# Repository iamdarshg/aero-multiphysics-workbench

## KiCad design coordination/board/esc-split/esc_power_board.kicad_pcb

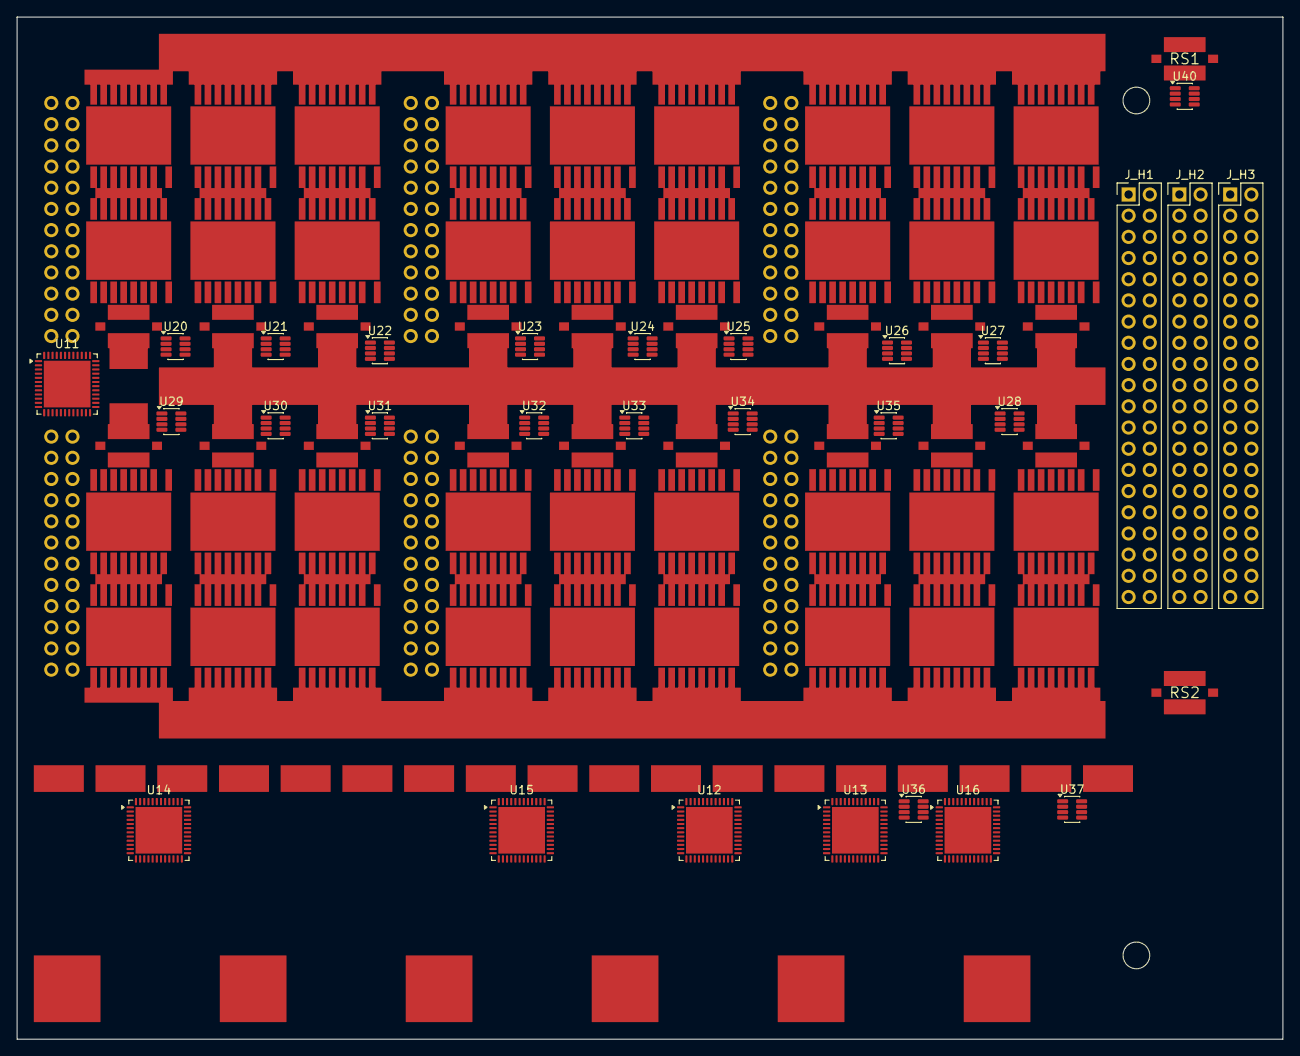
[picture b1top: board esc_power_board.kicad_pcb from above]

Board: 4 copper layers, 151.8 x 122.5 mm, 173 parts (0 on the bottom side), 41 nets, no tracks yet.

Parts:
BAR1, BAR2, BAR3: Busbar_land
C1, C2, C3, C4, C5, C6: 820uF_35V
CB1, CB2, CB3, CB4, CB5, CB6, CB7, CB8, CB9, CB10, CB11, CB12, CB13, CB14, CB15, CB16, CB17, CB18: copper
CN1, CN2, CN3, CN4, CN5, CN6, CN7, CN8, CN9, CN10, CN11, CN12, CN13, CN14, CN15, CN16, CN17, CN18: copper
CP1, CP2, CP3, CP4, CP5, CP6, CP7, CP8, CP9, CP10, CP11, CP12, CP13, CP14, CP15, CP16, CP17, CP18: copper
H4, H5: MountingHole_3.2
J1, J2, J3, J4, J5, J6: Conn_02x12_Pin
J_H1, J_H2, J_H3: TSW-120-15-G-D; PinHeader_2x20_P2.54mm_Vertical
P1, P2, P3, P4, P5, P6, P7, P8, P9, P10, P11, P12, P13, P14, P15, P16, P17, P18: MotorLand_6x4
Q1AH, Q1AL, Q1BH, Q1BL, Q1CH, Q1CL, Q2AH, Q2AL, Q2BH, Q2BL, Q2CH, Q2CL, Q3AH, Q3AL, Q3BH, Q3BL, Q3CH, Q3CL, Q4AH, Q4AL, Q4BH, Q4BL, Q4CH, Q4CL, Q5AH, Q5AL, Q5BH, Q5BL, Q5CH, Q5CL, Q6AH, Q6AL, Q6BH, Q6BL, Q6CH, Q6CL: IPTC014N10NM5
R1A, R1B, R1C, R2A, R2B, R2C, R3A, R3B, R3C, R4A, R4B, R4C, R5A, R5B, R5C, R6A, R6B, R6C: L500x 0.5m 10W
RS1, RS2: L500x 0.5m 10W
U11, U12, U13, U14, U15, U16: DRV8353; QFN-48-1EP_7x7mm_P0.5mm_EP5.6x5.6mm
U20, U21, U22, U23, U24, U25, U26, U27, U28, U29, U30, U31, U32, U33, U34, U35, U36, U37, U40: INA296A2; SOT-23-8

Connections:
AGND: J_H3.2, J_H3.4, J_H3.6, J_H3.8, J_H3.10, J_H3.12, J_H3.14, J_H3.16, J_H3.18, J_H3.20, J_H3.22, J_H3.24, J_H3.26, J_H3.28, J_H3.30, J_H3.32, J_H3.34, J_H3.36, J_H3.38
BATN: BAR2.1, CB1.1, CB2.1, CB3.1, CB4.1, CB5.1, CB6.1, CB7.1, CB8.1, CB9.1, CB10.1, CB11.1, CB12.1, CB13.1, CB14.1, CB15.1, CB16.1, CB17.1, CB18.1, R1A.2, R1B.2, R1C.2, R2A.2, R2B.2, R2C.2, R3A.2, R3B.2, R3C.2, R4A.1, R4B.1, R4C.1, R5A.1, R5B.1, R5C.1, R6A.1, R6B.1, R6C.1
BATN_K: R1A.4, R1B.4, R1C.4, R2A.4, R2B.4, R2C.4, R3A.4, R3B.4, R3C.4, R4A.3, R4B.3, R4C.3, R5A.3, R5B.3, R5C.3, R6A.3, R6B.3, R6C.3
BATP: BAR1.1, BAR3.1, CP1.1, CP2.1, CP3.1, CP4.1, CP5.1, CP6.1, CP7.1, CP8.1, CP9.1, CP10.1, CP11.1, CP12.1, CP13.1, CP14.1, CP15.1, CP16.1, CP17.1, CP18.1, Q1AH.9, Q1BH.9, Q1CH.9, Q2AH.9, Q2BH.9, Q2CH.9, Q3AH.9, Q3BH.9, Q3CH.9, Q4AH.9, Q4BH.9, Q4CH.9, Q5AH.9, Q5BH.9, Q5CH.9, Q6AH.9, Q6BH.9, Q6CH.9
DGND: J_H1.5, J_H1.6, J_H1.7, J_H1.8, J_H1.10, J_H1.12, J_H1.15, J_H1.16, J_H1.20, J_H1.23, J_H1.24, J_H1.27, J_H1.28, J_H1.32, J_H1.40, J_H2.4, J_H2.8, J_H2.12, J_H2.16, J_H2.20, J_H2.24, J_H2.28, J_H2.30, J_H2.34
M1_PHA: CN1.1, Q1AH.1, Q1AL.9
M1_PHB: CN2.1, Q1BH.1, Q1BL.9
M1_PHC: CN3.1, Q1CH.1, Q1CL.9
M1_SNA: Q1AL.1, R1A.1
M1_SNB: Q1BL.1, R1B.1
M1_SNC: Q1CL.1, R1C.1
M2_PHA: CN4.1, Q2AH.1, Q2AL.9
M2_PHB: CN5.1, Q2BH.1, Q2BL.9
M2_PHC: CN6.1, Q2CH.1, Q2CL.9
M2_SNA: Q2AL.1, R2A.1
M2_SNB: Q2BL.1, R2B.1
M2_SNC: Q2CL.1, R2C.1
M3_PHA: CN7.1, Q3AH.1, Q3AL.9
M3_PHB: CN8.1, Q3BH.1, Q3BL.9
M3_PHC: CN9.1, Q3CH.1, Q3CL.9
M3_SNA: Q3AL.1, R3A.1
M3_SNB: Q3BL.1, R3B.1
M3_SNC: Q3CL.1, R3C.1
M4_PHA: CN10.1, Q4AH.1, Q4AL.9
M4_PHB: CN11.1, Q4BH.1, Q4BL.9
M4_PHC: CN12.1, Q4CH.1, Q4CL.9
M4_SNA: Q4AL.1, R4A.2
M4_SNB: Q4BL.1, R4B.2
M4_SNC: Q4CL.1, R4C.2
M5_PHA: CN13.1, Q5AH.1, Q5AL.9
M5_PHB: CN14.1, Q5BH.1, Q5BL.9
M5_PHC: CN15.1, Q5CH.1, Q5CL.9
M5_SNA: Q5AL.1, R5A.2
M5_SNB: Q5BL.1, R5B.2
M5_SNC: Q5CL.1, R5C.2
M6_PHA: CN16.1, Q6AH.1, Q6AL.9
M6_PHB: CN17.1, Q6BH.1, Q6BL.9
M6_PHC: CN18.1, Q6CH.1, Q6CL.9
M6_SNA: Q6AL.1, R6A.2
M6_SNB: Q6BL.1, R6B.2
M6_SNC: Q6CL.1, R6C.2

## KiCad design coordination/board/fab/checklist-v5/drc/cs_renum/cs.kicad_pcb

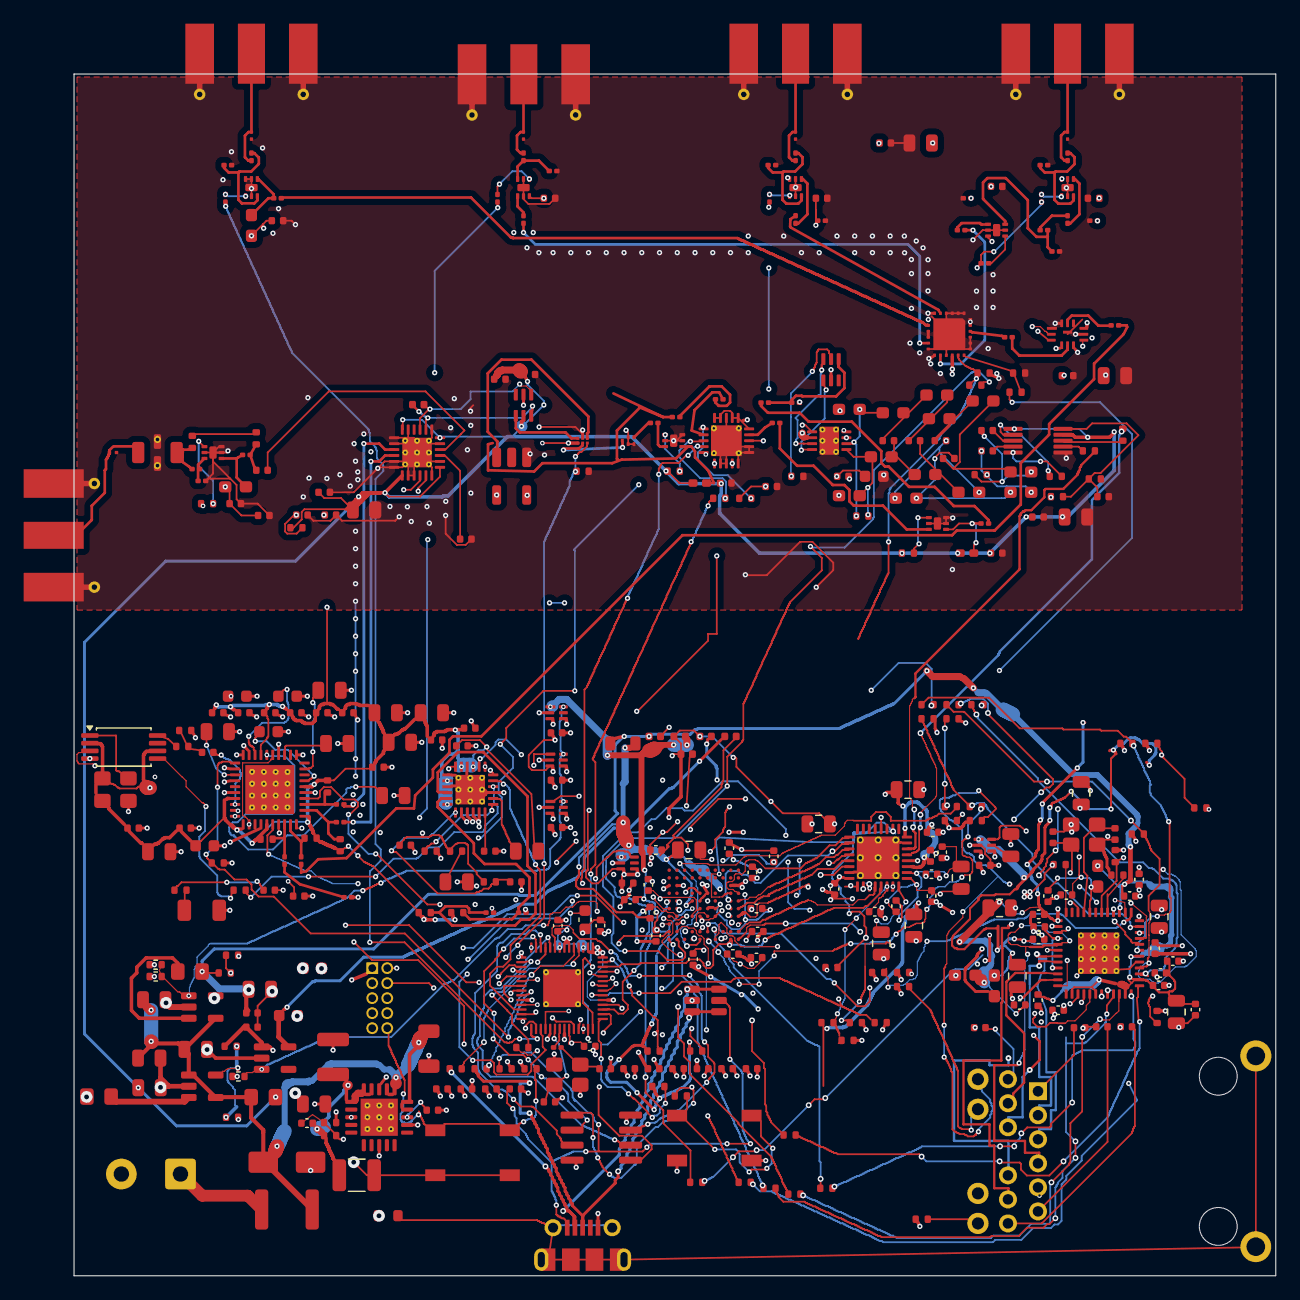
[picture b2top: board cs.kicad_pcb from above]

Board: 4 copper layers, 101.6 x 101.6 mm, 373 parts (0 on the bottom side), 260 nets.

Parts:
C1, C2, C4, C7: 22uF; C_0805_2012Metric
C3, C6, C41, C43, C45, C56, C57, C58, C61, C62, C65, C66, C67, C73, C83, C94, C106, C154, C159, C261, C279, C280, C281, C297, C300, C310: 10uF; C_0805_2012Metric
C5, C8, C23, C24, C25, C26, C27, C28, C40, C42, C44, C46, C47, C48, C50, C51, C52, C53, C54, C55, C60, C69, C76, C77, C78, C81, C82, C93, C100, C101, C105, C150, C151, C152, C153, C155, C174, C200, C214, C224, C225, C226, C227, C254, C255, C256, C260, C270, C272, C273, C274, C275, C276, C277, C278, C283, C284, C293, C295, C296, C298, C299, C302, C303, C304, C305, C307, C308, C309, C311, C312, C314, C316, C318, C319, C321, C322, C330, C331, C340, C341, C342, C343, C344, C347: 100nF; C_0402_1005Metric
C9, C22, C63, C64, C68, C247, C271: 1uF; C_0603_1608Metric
C10: 2.2uF; C_0603_1608Metric
C11: 22uF_10V_X7R; C_1206_3216Metric
C12, C346: 47uF_10V_X7R; C_1210_3225Metric
C20, C21: 15pF_C0G; C_0402_1005Metric
C70: 4.7nF_C0G; C_0402_1005Metric
C71: 100nF_C0G; C_1206_3216Metric
C72, C156, C301, C348: 10nF; C_0402_1005Metric
C74, C205: 470pF_C0G; C_0402_1005Metric
C75: 22nF_C0G; C_0805_2012Metric
C80, C213, C282: 100pF_C0G; C_0402_1005Metric
C102, C211, C212: 1nF_C0G; C_0402_1005Metric
C157, C158: 33pF_C0G; C_0402_1005Metric
C201, C202, C203, C204, C206, C207, C208, C210, C215, C223, C232, C233, C234, C235, C236, C237, C238, C245: 100pF_C0G; C_0201_0603Metric
C209, C219, C292, C2112: 0.2pF_C0G; C_0201_0603Metric
C216: 0.6pF_C0G; C_0201_0603Metric
C217: 0.8pF_C0G; C_0201_0603Metric
C218, C291: 0.5pF_C0G; C_0201_0603Metric
C246, C294, C2211: 1.0pF_C0G; C_0201_0603Metric
C262, C268: 51pF_C0G; C_0402_1005Metric
C264, C266: 56pF_C0G; C_0402_1005Metric
C306, C313, C323: 1uF; C_0402_1005Metric
C315, C317, C320: 2.2uF; C_0402_1005Metric
C345: 20nF_C0G_5%; C_0805_2012Metric
C2110: 22pF_C0G; C_0201_0603Metric
C2111: 0.3pF_C0G; C_0201_0603Metric
C2210: 2.2pF_C0G; C_0201_0603Metric
D1: SMAJ5.0A; D_SMA
D50, D60, D61, D62, D63: PESD1V0R1BCSF; SOD962-2_DSN0603
F1: 2.5A_PTC; Fuse_1812_4532Metric
FB1: 600R@100MHz_2A; Inductor_0805_HandSolder
FB30: 600R@100MHz; L_0603_1608Metric_Pad1.05x0.95mm_HandSolder
FB31, FB32: 120R@100MHz; L_0603_1608Metric_Pad1.05x0.95mm_HandSolder
FB33: BLM21SN300SN1D; L_0805_2012Metric
FB34: 220R@100MHz; L_0402_1005Metric
FB35, FB36, FB37, FB38: 120R@100MHz; L_0402_1005Metric
FL50: LFCN-2500+; MiniCircuits_FV1206
FL70: QPQ1909TR13; QPQ1909_1.4x1.2mm
J1: 5V_INPUT_ONLY; TerminalBlock_Phoenix_MKDS-1,5-2_1x02_P5.00mm_Horizontal
J10: USB_B_Micro; USB_Micro-B_Molex-105017-0001
J11: Cortex_SWD_10pin; PinHeader_2x05_P1.27mm_Vertical
J30: JK0654219NL; RJ45_Pulse_JK0654219NL_Horizontal
J50: RF_LOW_0.01_2.5GHz_OPTION; SMA_Molex_73251-1153_EdgeMount_Horizontal
J60: RF_HIGH_2.3_4.2GHz; SMA_Molex_73251-1153_EdgeMount_Horizontal
J61: RF_HIGH_4.2_6.8GHz; SMA_Molex_73251-1153_EdgeMount_Horizontal
J62: RF_HIGH_6.8_9.2GHz; SMA_Molex_73251-1153_EdgeMount_Horizontal
J63: RF_HIGH_8.0_10GHz; SMA_Molex_73251-1153_EdgeMount_Horizontal
L1, L2: 2.2uH_2.5A; Inductor_0805_HandSolder
L80, L83: 220nH; L_0603_1608Metric_Pad1.05x0.95mm_HandSolder
L84, L97: 33nH; L_0402_1005Metric_Pad0.77x0.64mm_HandSolder
L85, L86: 2.2uH; L_0603_1608Metric_Pad1.05x0.95mm_HandSolder
L87, L88, L95, L96: 200nH; L_0603_1608Metric_Pad1.05x0.95mm_HandSolder
L89, L90, L93, L94: 360nH; L_0603_1608Metric_Pad1.05x0.95mm_HandSolder
L91, L92: 390nH; L_0603_1608Metric_Pad1.05x0.95mm_HandSolder
L98: 2.7nH; L_0402_1005Metric
R1: 453k_0.1%; R_0402_1005Metric
R2, R4: 100k_0.1%; R_0402_1005Metric
R3: 101k_0.1%; R_0402_1005Metric
R5: 0; R_0603_1608Metric
R20, R21: 27R; R_0402_1005Metric
R22, R23, R146: 100k; R_0402_1005Metric
R30, R33, R134, R135, R136, R137, R138, R139, R140, R148: 4.7k; R_0402_1005Metric
R31, R51, R120, R121, R122, R123, R124, R125, R126, R127, R128, R129, R130, R131, R149: 33R; R_0402_1005Metric
R32, R60, R153, R156: 0R; R_0402_1005Metric
R40: 12.1k_1%; R_0402_1005Metric
R41, R141, R142, R143, R147: 10k; R_0402_1005Metric
R42, R43: 330R; R_0402_1005Metric
R50, R152: 150R_1%; R_0402_1005Metric
R52, R53, R54, R55: 50R; R_0402_1005Metric
R56, R93: 220R_1%; R_0402_1005Metric
R58: 4.7k_1%; R_0402_1005Metric
R59, R160, R161: 1k_1%; R_0402_1005Metric
R61: 1.5k_1%; R_0402_1005Metric
R70, R81: 499R_1%; R_0402_1005Metric
R71: 3.0R_1%; R_0402_1005Metric
R72: 33R_1%; R_0402_1005Metric
R73, R74: 25R_1%; R_0402_1005Metric
R75, R76, R77, R78, R144, R145: 10k_1%; R_0402_1005Metric
R79, R80: 100R_1%; R_0402_1005Metric
R90: 2.00k_1%; R_0402_1005Metric
R91: 1.00k_1%; R_0402_1005Metric
R92: 50R; R_0201_0603Metric
R94, R95: 51R; R_0402_1005Metric
R100, R105, R106, R107, R111: 0R; R_0201_0603Metric
R101: 1.5k; R_0201_0603Metric
R102: 200R; R_0201_0603Metric
R103, R112: 2.9k; R_0201_0603Metric
R132, R133: 2.2k; R_0402_1005Metric
R150: 1k; R_0201_0603Metric
R151: 1k; R_0402_1005Metric
R154: 30.3k_0.1%; R_0402_1005Metric
R155: 10k_0.1%; R_0402_1005Metric
R157, R159: 120k_1%; R_0402_1005Metric
R158: 100k_1%; R_0402_1005Metric
SW1: BOOTSEL; SW_SPST_TL3342
SW2: RESET; SW_SPST_TL3342
T50: 2450BL15B0200001E; Johanson_0805_6P_Balun
T60: TC1-1-13M+; Transformer_MiniCircuits_AT224-1A
T70: 2450BL15B0100001E; Johanson_0805_6P_Balun
U1, U2: TLV62569DBVR; SOT-23-5
U3: TLV75525PDBVR; SOT-23-5
U4: TPS7A8300ARGWT; Texas_RGW0020A_VQFN-20-1EP_5x5mm_P0.65mm_EP3.15x3.15mm_Ther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
U5, U6, U7: TPS389033DSER; WSON-6_1.5x1.5mm_P0.5mm
U8, U9: TPS389012DSER; WSON-6_1.5x1.5mm_P0.5mm
U10: RP2040; QFN-56-1EP_7x7mm_P0.4mm_EP3.2x3.2mm_ThermalVias
U11: W25Q16JVSNIQ; SOIC-8_3.9x4.9mm_P1.27mm
U12: USBLC6-2SC6; SOT-23-6
U20: LIF-MD6000-6JMG80I
U21: AD9215BCPZ-105; LFCSP-32-1EP_5x5mm_P0.5mm_EP3.6x3.6mm_ThermalVias
U30: KSZ9031RNXCA; QFN-48-1EP_7x7mm_P0.5mm_EP3.5x3.5mm_ThermalVias
U40: LMX2592RHAT; Texas_RHA0040B_VQFN-40-1EP_6x6mm_P0.5mm_EP4.15x4.15mm_Therm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
U41: ADF4360-1BCPZ; LFCSP-24-1EP_4x4mm_P0.5mm_EP2.5x2.5mm_ThermalVias
U42: CDCLVC1104PWR; TSSOP-8_4.4x3mm_P0.65mm
U50, U60: GRF4001; GRF_DFN6_1.5x1.5mm
U51: ADL5801ACPZ-R7; LFCSP-24-1EP_4x4mm_P0.5mm_EP2.5x2.5mm_ThermalVias
U61, U62, U66, U67: GRF2101; GRF_DFN6_1.5x1.5mm
U63: LTC5548IUDB; DFN-12-1EP_3x2mm_P0.5mm
U64: QPC6144TR13; QPC6144_LGA24_4x4mm
U70: BGS12WN6E6327; Infineon_TSNP6_1.1x0.7mm
U71, U75: GRF2013; GRF_DFN6_1.5x1.5mm
U72: PE4312C-Z; QFN-20-1EP_4x4mm_P0.5mm_EP2.6x2.6mm_ThermalVias
U73: LT5560EDD; DFN-8-1EP_3x3mm_P0.5mm_EP1.65x2.38mm_ThermalVias
U74: AD8351ARMZ; MSOP-10_3x3mm_P0.5mm
Y10: ABM8-272-T3_12MHz; Crystal_SMD_3225-4Pin_3.2x2.5mm
Y30: ECS-250-20-33-TR_25MHz; Crystal_SMD_3225-4Pin_3.2x2.5mm
Y40: SiT8209AC-23-33E-100.000000X; Oscillator_SMD_SiT_PQFN-4Pin_3.2x2.5mm

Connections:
+1V2_CORE: C7.1, C8.1, C52.1, C53.1, C54.1, C57.1, C303.1, C304.1, C305.1, FB30.1, FB32.1, FB33.1, FB34.1, L2.2, R3.1, U30.14, U30.18, U30.23, U30.26, U30.30, U30.39
+2V5_AUX: C10.1, FB38.1, U3.5
+3V3_ANA: C12.1, C40.1, C41.1, C44.1, C45.1, C60.1, C61.1, C69.1, C73.2, C76.1, C77.1, C78.1, C80.1, C81.1, C93.1, C94.1, C102.1, C224.1, C225.1, C226.1, C227.1, C247.1, C260.1, C261.1, C270.1, C271.1, C273.1, C274.1, C275.1, C276.1, C277.1, C278.1, C279.1, C280.1, C281.1, C293.1, C294.1, C346.1, C348.1, C2210.1, C2211.1, L80.1, L83.1, L85.1, L86.1, R52.1, R53.1, R54.1, R55.1, R75.1, R90.1, R94.1, R95.1, R154.1, U4.1, U4.19, U4.20, U21.27, U21.32, U40.7, U40.11, U40.15, U40.21, U40.26, U40.37, U41.2, U41.6, U41.21, U41.23, U42.2, U42.6, U61.6, U62.6, U63.9, U64.16, U66.6, U67.6, U73.2, U73.7, Y40.1, Y40.4
+3V3_DIG: C4.1, C5.1, C9.1, C23.1, C24.1, C25.1, C26.1, C27.1, C28.1, C42.1, C43.1, C50.1, C51.1, C56.1, C101.1, C302.1, C306.1, C307.1, C308.1, C309.1, C340.1, C341.1, C342.1, C343.1, C344.1, FB31.1, FB35.1, FB36.1, FB37.1, J11.1, L1.2, R1.1, R23.1, R41.1, R42.1, R43.1, R78.1, R132.1, R133.1, R134.1, R135.1, R136.1, R137.1, R141.1, R142.1, R157.1, R159.1, U3.1, U5.3, U5.4, U6.3, U6.4, U7.3, U7.4, U8.3, U8.4, U9.3, U9.4, U10.1, U10.10, U10.22, U10.33, U10.42, U10.43, U10.44, U10.48, U10.49, U11.8, U21.16, U30.16, U30.34, U30.40, U70.4, U72.6, U72.9, U72.13, U72.15, U72.16, U72.17, U72.19, U72.20
+5V_RF: C2.1, C82.1, C83.1, C100.1, C105.1, C106.1, C282.1, C283.1, C284.1, FB1.2, L84.1, L97.1, R61.1, R70.1, R81.1, T50.2, U51.7, U51.13, U51.18, U51.24, U74.1, U74.9
AD8351_IN_N: C255.2, U74.4
AD8351_IN_P: C254.2, U74.3
AD8351_OUT_N: R74.1, U74.7
AD8351_OUT_P: R73.1, U74.8
AD8351_RGP1: R72.1, U74.2
AD8351_RGP2: R72.2, U74.5
ADC_CLK: R31.2, U20.D9, U21.2
ADC_D0: U20.D10, U21.9
ADC_D1: U20.E9, U21.10
ADC_D2: U20.E10, U21.11
ADC_D3: U20.F9, U21.12
ADC_D4: U20.F10, U21.13
ADC_D5: U20.G9, U21.14
ADC_D6: U20.G10, U21.17
ADC_D7: U20.H9, U21.18
ADC_D8: U20.H10, U21.19
ADC_D9: U20.J10, U21.20
ADC_MODE: C156.1, R90.2, R91.1, U21.22
ADC_OR: U10.40, U20.K9, U21.21
ADC_PDWN: R147.1, U10.34, U21.4
ADC_REFB: C47.1, C154.2, C155.2, U21.25
ADC_REFT: C48.1, C154.1, C155.1, U21.26
ADC_SENSE: R32.1, U21.23
ADC_VCM: C256.1, R75.2, R76.1, U74.10
ADC_VIN_N: R74.2, U21.30
ADC_VIN_P: R73.2, U21.29
ADC_VREF: C46.1, C159.1, U21.24
ADF_CC: C72.1, U41.12
ADF_CLK: U10.12, U41.17
ADF_CN: C73.1, U41.14
ADF_CPOUT: C74.1, R59.1, R93.1, U41.24
ADF_DATA: U10.13, U41.18
ADF_LE: U10.11, U41.19
ADF_LF1: C75.1, R59.2
ADF_LO2_N_RAW: C207.1, R95.2, U41.5
ADF_LO2_P_RAW: C206.1, R94.2, U41.4
ADF_LOCK: U10.39, U41.20
ADF_REF: R51.2, U41.16
ADF_RSET: R58.1, U41.13
ADF_VTUNE: C205.1, R93.2, U41.7
ADL_DETO: C214.1, U51.11
ADL_RF_DRIVE: C211.2, U51.16
ADL_RF_UNUSED: C212.1, U51.15
ADL_VSET: C213.1, R61.2, U51.10
ANA_NR_SS: C347.1, U4.13
AUX_EN: R159.2, U3.3, U8.6
BOOTSEL_SWITCH: R151.2, SW1.D36_0, SW1.D36_1
CHASSIS_GND: J10.D55_5, J10.D55_6, J10.D55_7, J10.D55_8, J10.D55_9, J10.D55_10, J10.D55_11, J10.D55_12, J30.D14_18, J30.D14_19, R5.2
CORE_EN: R157.2, R158.1, U2.1, U5.6, U6.6, U7.6
DSA_C16: R78.2, U72.1
DSA_CLK: U10.28, U72.4
DSA_DATA: R77.1, U10.27
DSA_DATA_PIN: R77.2, U72.3
DSA_LE: U10.18, U72.5
FB_1V2: R3.2, R4.1, U2.5
FB_3V3: R1.2, R2.1, U1.5
FB_ANA: C348.2, R154.2, R155.1, U4.3
FPGA_AUX_2V5: C323.1, FB38.2, U20.D5
FPGA_CDONE: R33.2, U10.41, U20.J2
FPGA_PLL_1V2: C313.1, C314.1, FB34.2, U20.G6
FPGA_RESET_N: R30.2, U10.29, U20.H2
FPGA_SPI_CS_N: R148.2, U10.5, U20.H1
FPGA_SPI_MISO: U10.4, U20.K1
FPGA_SPI_MOSI: U10.3, U20.G1
FPGA_SPI_SCK: R149.2, U20.J1
FPGA_SPI_SCK_MCU: R149.1, U10.2
FPGA_VCCIO0_3V3: C315.1, C316.1, FB35.2, R30.1, R33.1, R148.1, U5.1, U20.F4
FPGA_VCCIO1_3V3: C317.1, C318.1, C319.1, FB36.2, U6.1, U20.F5, U20.G4
FPGA_VCCIO2_3V3: C320.1, C321.1, C322.1, FB37.2, U7.1, U20.F6, U20.F7
FPGA_VCC_1V2: C310.1, C311.1, C312.1, FB33.2, U8.1, U20.E4, U20.E6
GND: C1.2, C2.2, C3.2, C4.2, C5.2, C6.2, C7.2, C8.2, C9.2, C10.2, C11.2, C12.2, C20.2, C21.2, C22.2, C23.2, C24.2, C25.2, C26.2, C27.2, C28.2, C40.2, C41.2, C42.2, C43.2, C44.2, C45.2, C46.2, C47.2, C48.2, C50.2, C51.2, C52.2, C53.2, C54.2, C55.2, C56.2, C57.2, C58.2, C60.2, C61.2, C62.2, C63.2, C64.2, C65.2, C66.2, C67.2, C68.2, C69.2, C70.2, C71.2, C72.2, C74.2, C75.2, C76.2, C77.2, C78.2, C80.2, C81.2, C82.2, C83.2, C93.2, C94.2, C100.2, C101.2, C102.2, C105.2, C106.2, C150.2, C151.2, C152.2, C153.2, C156.2, C157.2, C158.2, C159.2, C174.2, C205.2, C209.2, C212.2, C213.2, C214.2, C219.2, C224.2, C225.2, C226.2, C227.2, C246.2, C247.2, C256.2, C260.2, C261.2, C270.2, C271.2, C272.2, C273.2, C274.2, C275.2, C276.2, C277.2, C278.2, C279.2, C280.2, C281.2, C282.2, C283.2, C284.2, C292.2, C293.2, C294.2, C295.2, C296.2, C297.2, C298.2, C299.2, C300.2, C301.2, C302.2, C303.2, C304.2, C305.2, C306.2, C307.2, C308.2, C309.2, C310.2, C311.2, C312.2, C313.2, C314.2, C315.2, C316.2, C317.2, C318.2, C319.2, C320.2, C321.2, C322.2, C323.2, C330.2, C331.2, C340.2, C341.2, C342.2, C343.2, C344.2, C345.2, C346.2, C347.2, C2110.2, C2111.2, C2112.2, C2210.2, C2211.2, D1.2, D50.2, D60.2, D61.2, D62.2, D63.2, FL50.D33_1, FL50.D33_2, FL50.D33_4, FL50.D33_5, FL70.2, FL70.3, FL70.5, J1.2, J10.5, J11.3, J11.5, J11.9, J50.D40_1, J50.D40_2, J50.D40_3, J50.D40_4, J50.D40_5, J50.D40_6, J50.D40_7, J50.D40_8, J50.D40_9, J50.D40_10, J60.D21_1, J60.D21_2, J60.D21_3, J60.D21_4, J60.D21_5, J60.D21_6, J60.D21_7, J60.D21_8, J60.D21_9, J60.D21_10, J61.D59_1, J61.D59_2, J61.D59_3, J61.D59_4, J61.D59_5, J61.D59_6, J61.D59_7, J61.D59_8, J61.D59_9, J61.D59_10, J62.D63_1, J62.D63_2, J62.D63_3, J62.D63_4, J62.D63_5, J62.D63_6, J62.D63_7, J62.D63_8, J62.D63_9, J62.D63_10, J63.D20_1, J63.D20_2, J63.D20_3, J63.D20_4, J63.D20_5, J63.D20_6, J63.D20_7, J63.D20_8, J63.D20_9, J63.D20_10, R2.2, R4.2, R5.1, R22.2, R32.2, R40.2, R58.2, R71.2, R76.2, R91.2, R92.2, R138.2, R139.2, R140.2, R143.2, R144.2, R145.2, R146.2, R147.2, R152.2, R155.2, R158.2, SW1.D36_2, SW1.D36_3, SW2.D37_2, SW2.D37_3, T50.5, T60.3, T70.5, U1.2, U2.2, U3.2, U4.8, U4.12, U4.18, U4.D62_24, U4.D62_25, U4.D62_26, U4.D62_27, U4.D62_28, U4.D62_29, U4.D62_30, U4.D62_31, U4.D62_32, U4.D62_33, U4.D62_34, U5.2, U6.2, U7.2, U8.2, U9.2, U10.19, U10.D3_60, U10.D3_61, U10.D3_62, U10.D3_63, U10.D3_64, U10.D3_65, U11.4, U12.2, U20.C1, U20.C2, U20.C9, U20.C10, U20.D6, U20.E5, U20.G2, U20.G5, U20.G7, U21.15, U21.28, U21.31, U21.D7_36, U21.D7_37, U21.D7_38, U21.D7_39, U21.D7_40, U21.D7_41, U21.D7_42, U21.D7_43, U21.D7_44, U21.D7_45, U21.D7_46, U30.29, U30.D11_57, U30.D11_58, U30.D11_59, U30.D11_60, U30.D11_61, U30.D11_62, U30.D11_63, U30.D11_64, U30.D11_65, U30.D11_66, U30.D11_67, U30.D11_68, U30.D11_69, U30.D11_70, U30.D11_71, U30.D11_72, U30.D11_73, U30.D11_74, U40.2, U40.4, U40.6, U40.13, U40.14, U40.25, U40.31, U40.34, U40.39, U40.40, U40.D38_49, U40.D38_50, U40.D38_51, U40.D38_52, U40.D38_53, U40.D38_54, U40.D38_55, U40.D38_56, U40.D38_57, U40.D38_58, U40.D38_59, U40.D38_60, U40.D38_61, U40.D38_62, U40.D38_63, U40.D38_64, U40.D38_65, U40.D38_66, U41.1, U41.3, U41.8, U41.9, U41.10, U41.11, U41.15, U41.22, U41.D17_28, U41.D17_29, U41.D17_30, U41.D17_31, U41.D17_32, U41.D17_33, U41.D17_34, U41.D17_35, U41.D17_36, U41.D17_37, U41.D17_38, U42.4, U50.2, U50.5, U50.6, U50.7, U51.1, U51.2, U51.5, U51.6, U51.8, U51.9, U51.12, U51.14, U51.17, U51.19, U51.23, U51.D51_28, U51.D51_29, U51.D51_30, U51.D51_31, U51.D51_32, U51.D51_33, U51.D51_34, U51.D51_35, U51.D51_36, U51.D51_37, U51.D51_38, U60.2, U60.5, U60.6, U60.7, U61.2, U61.5, U61.7, U62.2, U62.5, U62.7, U63.1, U63.4, U63.6, U63.8, U63.10, U63.12, U63.13, U64.1, U64.2, U64.3, U64.4, U64.6, U64.7, U64.9, U64.10, U64.12, U64.13, U64.15, U64.19, U64.20, U64.21, U64.23, U64.24, U64.25, U66.2, U66.5, U66.7, U67.2, U67.5, U67.7, U70.2, U71.2, U71.5, U71.6, U71.7, U72.7, U72.8, U72.10, U72.11, U72.12, U72.18, U72.D50_24, U72.D50_25, U72.D50_26, U72.D50_27, U72.D50_28, U72.D50_29, U73.D9_12, U73.D9_13, U73.D9_14, U73.D9_15, U73.D9_16, U73.D9_17, U73.D9_18, U73.D9_19, U74.6, U75.2, U75.5, U75.6, U75.7, Y10.2, Y10.4, Y30.2, Y30.4, Y40.2
GRF2013B_ENABLE: R81.2, U75.1
GRF2013B_RFOUT_VDD: C238.1, L97.2, U75.4
GRF2013_ENABLE: R70.2, U71.1
GRF2013_RFIN: C234.2, U71.3
GRF2013_RFOUT_VDD: C235.1, L84.2, U71.4
HF_BYPASS: R153.2, R156.1
HSW_V1: R160.1, U10.31
HSW_V1_CHIP: R144.1, R160.2, U64.17
HSW_V2: R161.1, U10.32
HSW_V2_CHIP: R145.1, R161.2, U64.18
IF2_F1_N: C262.2, L88.2, L90.1
IF2_F1_P: C262.1, L87.2, L89.1
IF2_F2_N: C264.2, L90.2, L92.1
IF2_F2_P: C264.1, L89.2, L91.1
IF2_F3_N: C266.2, L92.2, L94.1
IF2_F3_P: C266.1, L91.2, L93.1
IF2_F4_N: C268.2, L94.2, L96.1
IF2_F4_P: C268.1, L93.2, L95.1
IF2_LPF_N: C255.1, L96.2, R80.2
IF2_LPF_P: C254.1, L95.2, R80.1
IF2_N: L86.2, L88.1, R79.2, U73.5
IF2_P: L85.2, L87.1, R79.1, U73.6
IF_BAW_OUT: C234.1, FL70.4
IF_DSA_GAINED: C238.2, C245.1
IF_DSA_OUT: C237.2, U75.3
IF_GAIN_OUT: C235.2, C236.1
IF_HIGH_N: T60.4, U63.3
IF_HIGH_P: T60.6, U63.2
IF_HIGH_SE: T60.1, U70.1
IF_LOW_N: L98.2, T50.4, U51.21
IF_LOW_P: L98.1, T50.3, U51.20
IF_LOW_SE: T50.1, U70.3
IF_PATH_SEL: R146.1, U10.30, U70.6
IF_SELECTED: FL70.1, U70.5
LMX_CE: R143.1, U10.9, U40.1
LMX_CSB: U10.8, U40.24
LMX_LF_DAMP: C71.1, R56.2
LMX_LOCK: U10.38, U40.20
LMX_LO_HIGH_N_RAW: C202.1, R53.2, U40.18
LMX_LO_HIGH_P_RAW: C201.1, R52.2, U40.19
LMX_LO_LOW_N_RAW: C204.1, R55.2, U40.22
LMX_LO_LOW_P_RAW: C203.1, R54.2, U40.23
LMX_REF: C200.2, U40.8
LMX_REF_N: C272.1, U40.9
LMX_REF_PRE: C200.1, R50.2, R152.1
LMX_VARAC: C66.1, U40.33
LMX_VBIAS1: C62.1, U40.3
LMX_VBIAS2: C64.1, U40.27
LMX_VREF: C67.1, U40.36
LMX_VREF2: C65.1, U40.29
LMX_VREG: C68.1, U40.38
LMX_VREG_IN: C63.1, U40.10
LMX_VTUNE: C70.1, R56.1, U40.12, U40.35
LNA_EN_H1: R100.1, U10.15
LNA_EN_H2: R101.1, U10.16
LNA_EN_H3: R102.1, U10.17
LNA_EN_H4: R103.1, R112.1, U10.35
LNA_EN_LOW: R60.1, U10.14
LNA_EN_LOW_IC: R60.2, U50.1
LO2_N: C207.2, U73.1
LO2_P: C206.2, U73.8
LO_HIGH_N_TERM: C202.2, R92.1
LO_HIGH_P: C201.2, C233.1
LO_LOW_N: C204.2, U51.4
LO_LOW_P: C203.2, U51.3
LTC_LO_IN: C233.2, U63.11
LTC_RF_IN: C232.2, U63.5
LT_INPUT_CT: R71.1, T70.2
LT_INPUT_SE: C245.2, C246.1, T70.1
LT_IN_N: T70.4, U73.4
LT_IN_P: T70.3, U73.3
MAG_CT1: C150.1, J30.12
MAG_CT2: C151.1, J30.6
MAG_CT3: C152.1, J30.1
MAG_CT4: C153.1, J30.7
MAG_LED1_A: J30.16, R42.2
MAG_LED2_A: J30.14, R43.2
MDC: U20.J6, U30.36
MDIO: R132.2, U20.K7, U30.37
MDI_A_N: J30.10, U30.3
MDI_A_P: J30.11, U30.2
MDI_B_N: J30.5, U30.6
MDI_B_P: J30.4, U30.5
MDI_C_N: J30.2, U30.8
MDI_C_P: J30.3, U30.7
MDI_D_N: J30.9, U30.11
MDI_D_P: J30.8, U30.10
MIXER_EN_HIGH: U10.36, U63.7
PE4312_RF1: C236.2, U72.2
PE4312_RF2: C237.1, U72.14
PHY_AVDDH_3V3: C295.1, C296.1, C297.1, FB31.2, U30.1, U30.12
PHY_AVDDL_1V2: C298.1, C299.1, C300.1, FB32.2, U9.1, U30.4, U30.9
PHY_CLK125_NDO: R140.1, U30.41
PHY_INT_N: R133.2, U20.K2, U30.38
PHY_ISET: R40.1, U30.48
PHY_LED1: J30.15, R141.2, U30.17
PHY_LED2: J30.13, R142.2, U30.15
PHY_PLL_1V2: C55.1, C58.1, C301.1, FB30.2, U30.44
PHY_RESET_CT: C345.1, U9.5
PHY_RESET_N: R41.2, U9.6, U10.37, U30.42
PHY_XI: C157.1, U30.46, Y30.1
PHY_XO: C158.1, U30.45, Y30.3
QSPI_SCLK: U10.52, U11.6
QSPI_SD0: U10.53, U11.5
QSPI_SD1: U10.55, U11.2
QSPI_SD2: U10.54, U11.3
QSPI_SD3: U10.51, U11.7
QSPI_SS_N: R151.1, U10.56, U11.1
REF_100M_ADC: R31.1, U42.3
REF_100M_ADF: R51.1, U42.5
REF_100M_LMX: R50.1, U42.8
REF_100M_OSC: U42.1, Y40.3
RF_HA_ENABLE: R100.2, U60.1
RF_HA_IN: C215.1, D60.1, J60.1
RF_HA_LNA_IN: C215.2, C219.1, U60.3
RF_HA_LNA_OUT: C223.2, U64.8
RF_HA_LNA_OUT_RAW: C223.1, L83.2, U60.4
RF_HB_ENABLE: R101.2, U61.1
RF_HB_IN: C216.1, D61.1, J61.1
RF_HB_LNA_IN: C216.2, C2110.1, U61.3
RF_HB_LNA_OUT: R105.2, U64.11
RF_HB_LNA_OUT_RAW: R105.1, U61.4
RF_HC_ENABLE: R102.2, U62.1
RF_HC_IN: C217.1, D62.1, J62.1
RF_HC_LNA_IN: C217.2, C2111.1, U62.3
RF_HC_LNA_OUT: R106.2, U64.5
RF_HC_LNA_OUT_RAW: R106.1, U62.4
RF_HD2_ENABLE: R112.2, U67.1
RF_HD_ENABLE: R103.2, U66.1
RF_HD_IN: C218.1, D63.1, J63.1
RF_HD_LNA1_OUT: C291.1, R107.2
RF_HD_LNA2_IN: C291.2, C292.1, U67.3
RF_HD_LNA2_OUT_RAW: R111.1, U67.4
RF_HD_LNA_IN: C218.2, C2112.1, U66.3
RF_HD_LNA_OUT: R111.2, U64.14
RF_HD_LNA_OUT_RAW: R107.1, U66.4
RF_HIGH_SWITCHED: C232.1, U64.22
RF_LOW_FILT: C208.1, FL50.3, R153.1
RF_LOW_IN: D50.1, FL50.1, J50.1
RF_LOW_LNA_IN: C208.2, C209.1, U50.3
RF_LOW_LNA_OUT: C210.2, C211.1, R156.2
RF_LOW_LNA_OUT_RAW: C210.1, L80.2, U50.4
RGMII_RXC: R131.1, R138.1, U30.35
RGMII_RXC_FPGA: R131.2, U20.K6
RGMII_RXD0: R126.1, R137.2, U30.32
RGMII_RXD0_FPGA: R126.2, U20.K8
RGMII_RXD1: R127.1, R136.2, U30.31
RGMII_RXD1_FPGA: R127.2, U20.J5
RGMII_RXD2: R128.1, R135.2, U30.28
RGMII_RXD2_FPGA: R128.2, U20.K10
RGMII_RXD3: R129.1, R134.2, U30.27
RGMII_RXD3_FPGA: R129.2, U20.K4
RGMII_RX_DV: R130.1, R139.1, U30.33
RGMII_RX_DV_FPGA: R130.2, U20.K5
RGMII_TXC: R125.2, U30.24
RGMII_TXC_FPGA: R125.1, U20.J7
RGMII_TXD0: R120.2, U30.19
RGMII_TXD0_FPGA: R120.1, U20.E1
RGMII_TXD1: R121.2, U30.20
RGMII_TXD1_FPGA: R121.1, U20.E2
RGMII_TXD2: R122.2, U30.21
RGMII_TXD2_FPGA: R122.1, U20.F1
RGMII_TXD3: R123.2, U30.22
RGMII_TXD3_FPGA: R123.1, U20.F2
RGMII_TX_EN: R124.2, U30.25
RGMII_TX_EN_FPGA: R124.1, U20.J3
RP_CORE: C22.1, C330.1, C331.1, U10.23, U10.45, U10.50
RP_RUN: J11.10, R23.2, SW2.D37_0, SW2.D37_1, U10.26
RP_XIN: C20.1, U10.20, Y10.1
RP_XOUT: C21.1, R150.2, Y10.3
RP_XOUT_DRIVE: R150.1, U10.21
SWD_CLK: J11.4, U10.24
SWD_IO: J11.2, U10.25
SW_1V2: L2.1, U2.3
SW_3V3: L1.1, U1.3
SYNTH_SCK: U10.6, U40.16
SYNTH_SDI: U10.7, U40.17
USB_DM: R20.2, U10.46
USB_DM_CONN: J10.2, R20.1, U12.1, U12.6
USB_DP: R21.2, U10.47
USB_DP_CONN: J10.3, R21.1, U12.3, U12.4
USB_VBUS_SENSE: C174.1, J10.1, R22.1, U12.5
VIN_5V: F1.1, J1.1
VIN_FUSED: C1.1, C3.1, C6.1, C11.1, D1.1, F1.2, FB1.1, U1.1, U1.4, U2.4, U4.14, U4.15, U4.16, U4.17
